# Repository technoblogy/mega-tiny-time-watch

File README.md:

# Mega Tiny Time Watch
A watch based on an ATtiny414, showing the time analogue-style on 12 LEDs.
For more information see: http://www.technoblogy.com/show?2OKF.

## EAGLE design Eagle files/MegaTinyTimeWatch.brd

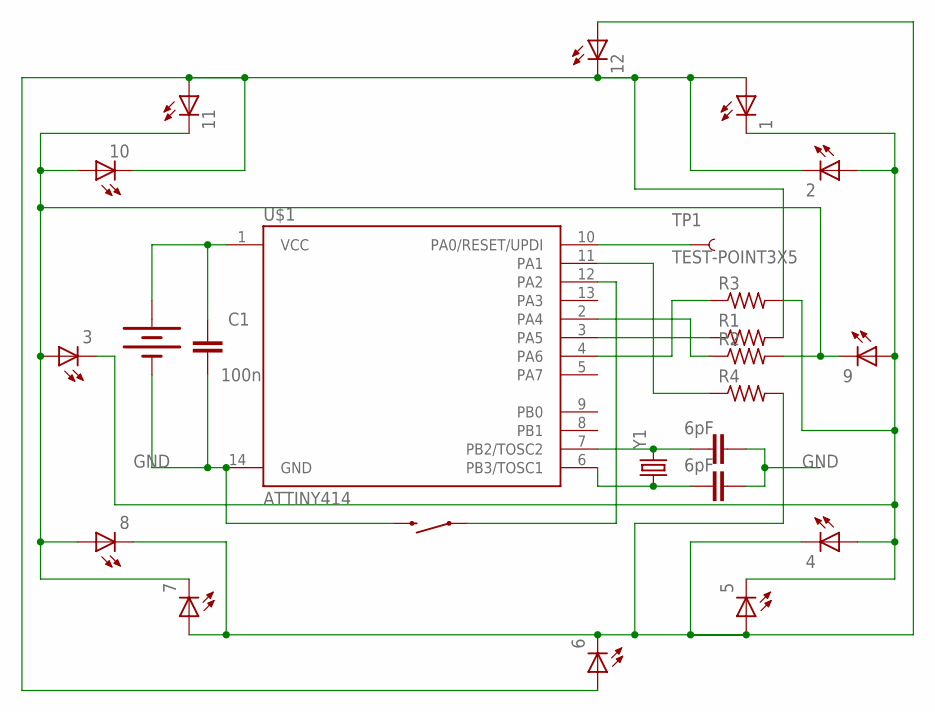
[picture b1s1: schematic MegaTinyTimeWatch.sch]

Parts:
1, 2, 3, 4, 5, 6, 7, 8, 9, 10, 11, 12: LEDCHIPLED_0805; CHIPLED_0805
BAT1: 20mm coincell; BATTCON_20MM_4LEGS
C1: 100n; 0603-CAP
C2, C12: 6pF; 0603-CAP
R1, R2, R3, R4: R-US_M0805; M0805
S2: SWITCH-MOMENTARY-2SMD; TACTILE-SWITCH-SMD
TP1: TEST-POINT3X5; PAD.03X.05
U$1: ATTINY414; SO14
Y1: CRYSTAL32-SMD-MELF; CRYSTAL-32KHZ-SMD-MELF

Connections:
GND: BAT1.NEGATIVE (-), C1.2, C2.1, C12.1, S2.3 (2), U$1.14 (GND)
unnamed: 1.C, 2.A, 3.C, 4.A, 5.C, 9.A, R3.2
unnamed: 4.C, 5.A, 6.C, 7.A, 8.C, 12.A, R4.2
unnamed: 3.A, 7.C, 8.A, 9.C, 10.A, 11.C, R2.2
unnamed: 1.A, 2.C, 6.A, 10.C, 11.A, 12.C, R1.2
unnamed: R3.1, U$1.4 (PA6)
unnamed: S2.1, U$1.12 (PA2)
unnamed: R2.1, U$1.2 (PA4)
unnamed: R4.1, U$1.11 (PA1)
unnamed: BAT1.POSITIVE@1 (+), BAT1.POSITIVE@2 (+), BAT1.POSITIVE@3 (+), BAT1.POSITIVE@4 (+), C1.1, U$1.1 (VCC)
unnamed: TP1.P$1, U$1.10 (PA0/RESET/UPDI)
unnamed: C12.2, U$1.7 (PB2/TOSC2), Y1.X2 (2)
unnamed: R1.1, U$1.3 (PA5)
unnamed: C2.2, U$1.6 (PB3/TOSC1), Y1.X1 (1)

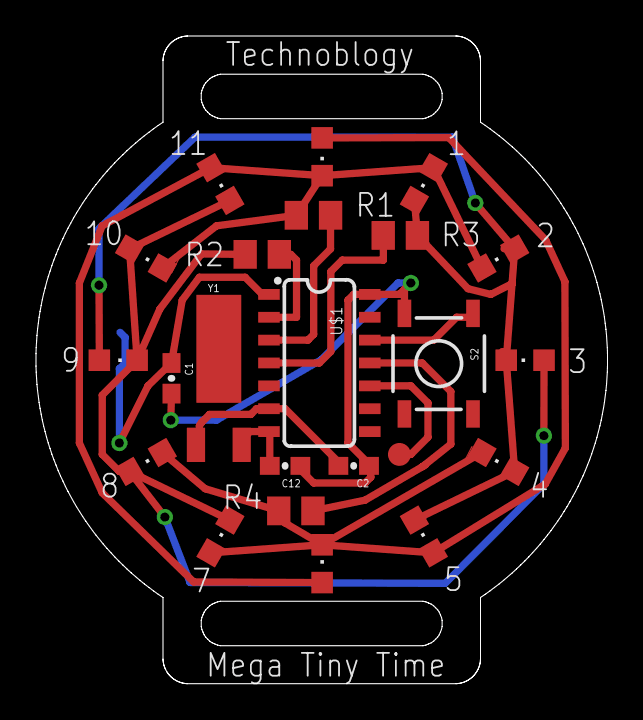
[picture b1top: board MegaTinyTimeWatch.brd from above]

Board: 2 copper layers, 31.7 x 36.0 mm, 24 parts (1 on the bottom side), 14 nets.

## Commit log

2020-01-07 Version 1 - 7th January 2020
2021-03-04 Version 2 - 8th November 2020
    Fixes problems - see original article

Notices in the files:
parts and their libraries:
SparkFun-Electromechanical: Licensing: Creative Commons ShareAlike 4.0 International - https://creativecommons.org/licenses/by-sa/4.0
SparkFun-Capacitors: Licensing: CC v3.0 Share-Alike You are welcome to use this library for commercial purposes.
